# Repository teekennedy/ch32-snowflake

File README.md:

# CH32 Snowflake

A holiday snowflake with RGB LEDs, driven by the infamous CH32V003 microcontroller.

This is my first ever PCB design, and I borrowed heavily from [ch32-fireplace](https://github.com/johanwheeler/ch32-fireplace/tree/main) for snippets of schematic and code.

## PCB Shape

The snowflake shape was designed in OpenSCAD using the [BOSL2 library](https://github.com/BelfrySCAD/BOSL2).
If you want to view or make changes to the shape, I highly recommend installing the nightly version of openSCAD.

## KiCad Project

The KiCad project was designed with help from the [jlcpcb-tools plugin](https://github.com/Bouni/kicad-jlcpcb-tools).
If you plan to send this board to JLCPCB, be sure to import [corrections.csv](./board/jlcpcb/corrections.csv) before generating your pick and place file.
It has corrections for both the CH32V003 (90 degrees CCW rotation) and the TPS61002 boost converter (which is offset from where it should be).

I did my best to choose Basic parts where possible, to help keep the cost of the economic PCB assembly down.
Then I went with an ENIG coating and couldn't use economic PCBA anyway. Oh well.

## Firmware

In order to flash the firmware, you need to setup your build environment for [ch32fun](https://github.com/cnlohr/ch32fun).
See [their installation wiki](https://github.com/cnlohr/ch32fun/wiki/Installation) for instructions.

Next, build the `minichlink` utility.
Ensure the ch32fun submodule is initialized `git submodule update --init`.
Then, from the software/ch32fun/minichlink directory, run `make`.
If you have your RISC-V toolchain installed properly, it should build.

Now you can go to the software/src directory and run `make` to compile and flash the binary.

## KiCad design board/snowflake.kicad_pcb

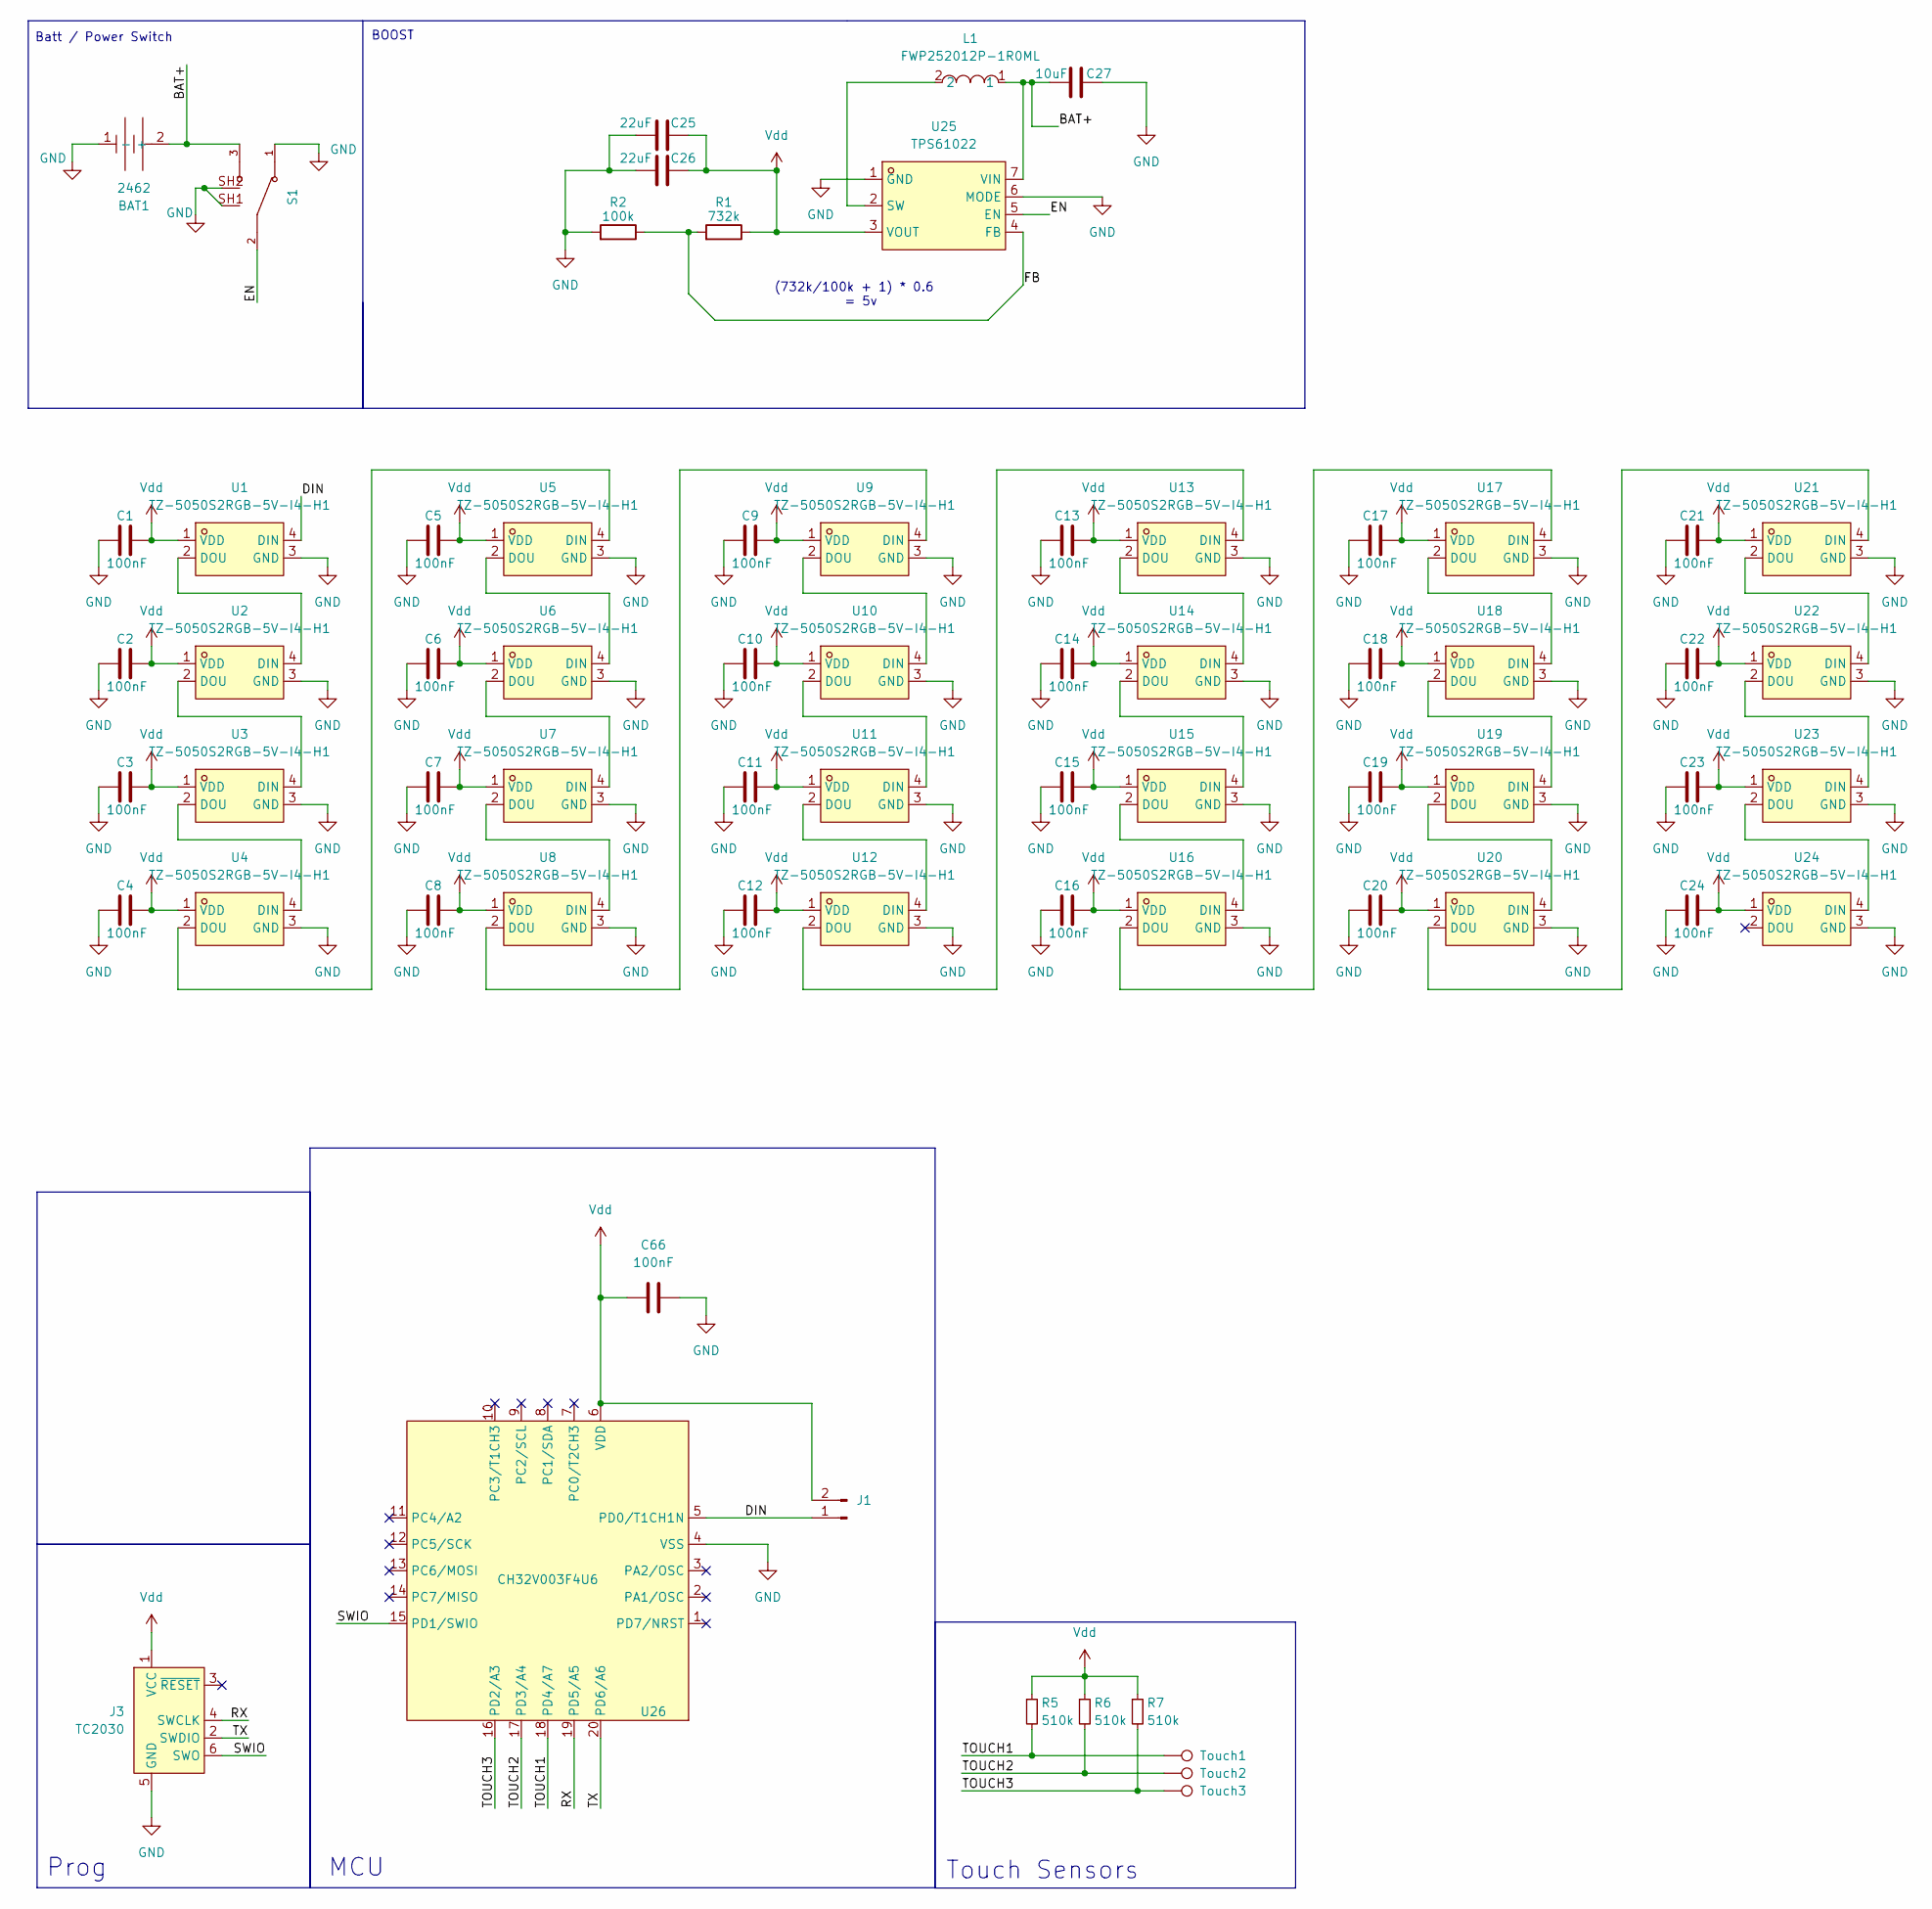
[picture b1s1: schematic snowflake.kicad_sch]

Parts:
BAT1: 2462; BAT-TH_2P-P14.50_2462; LCSC Part C3029547
C1, C2, C3, C4, C5, C6, C7, C8, C9, C10, C11, C12, C13, C14, C15, C16, C17, C18, C19, C20, C21, C22, C23, C24, C66: 100nF; C_0603_1608Metric; LCSC C14663
C25, C26: 22uF; C_0603_1608Metric; LCSC C59461
C27: 10uF; C_0603_1608Metric; LCSC C19702
J1: Conn_01x02_Pin; PinHeader_1x02_P2.54mm_Vertical
J3: TC2030; Tag-Connect_TC2030-IDC-NL_2x03_P1.27mm_Vertical
L1: FWP252012P-1R0ML; IND-SMD_L2.5-W2.0_YXMBL252010P; LCSC C5179444
R1: 732k; R_0603_1608Metric; LCSC C22961
R2: 100k; R_0402_1005Metric; LCSC C25741
R5, R6, R7: 510k; R_0603_1608Metric; MPN C23203; LCSC C23192
S1: SLW-1277545-3A-RA-N-D; SW_SLW-1277545-3A-RA-N-D; PARTREV 1.01
TP5: Touch1; TouchPad
TP6: Touch2; TouchPad
TP7: Touch3; TouchPad
U1, U2, U3, U4, U5, U6, U7, U8, U9, U10, U11, U12, U13, U14, U15, U16, U17, U18, U19, U20, U21, U22, U23, U24: TZ-5050S2RGB-5V-I4-H1; LED-SMD_4P-L5.0-W5.0-TL_WS2812B-B; LCSC C26167850
U25: TPS61022; VQFN-7_L2.0-W2.0-P0.55-TL_RWU; LCSC C915088
U26: CH32V003F4U6; QFN-20_L3.0-W3.0-P0.40-TL-EP1.7; MPN C5299908; LCSC C5299908

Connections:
/BAT+: BAT1.2 (+), C27.2, L1.1, S1.3, U25.7 (VIN)
/DIN: J1.1, U1.4 (DIN), U26.5 (PD0/T1CH1N)
/EN: S1.2, U25.5 (EN)
/FB: R1.2, R2.1, U25.4 (FB)
/RX: J3.4 (SWCLK), U26.19 (PD5/A5)
/SWIO: J3.6 (SWO), U26.15 (PD1/SWIO)
/TOUCH1: R5.2, TP5.1, U26.18 (PD4/A7)
/TOUCH2: R6.2, TP6.1, U26.17 (PD3/A4)
/TOUCH3: R7.2, TP7.1, U26.16 (PD2/A3)
/TX: J3.2 (SWDIO), U26.20 (PD6/A6)
GND: BAT1.1 (-), C1.1, C2.1, C3.1, C4.1, C5.1, C6.1, C7.1, C8.1, C9.1, C10.1, C11.1, C12.1, C13.1, C14.1, C15.1, C16.1, C17.1, C18.1, C19.1, C20.1, C21.1, C22.1, C23.1, C24.1, C25.2, C26.2, C27.1, C66.2, J3.5 (GND), R2.2, S1.1, S1.SH1, S1.SH2, U1.3 (GND), U2.3 (GND), U3.3 (GND), U4.3 (GND), U5.3 (GND), U6.3 (GND), U7.3 (GND), U8.3 (GND), U9.3 (GND), U10.3 (GND), U11.3 (GND), U12.3 (GND), U13.3 (GND), U14.3 (GND), U15.3 (GND), U16.3 (GND), U17.3 (GND), U18.3 (GND), U19.3 (GND), U20.3 (GND), U21.3 (GND), U22.3 (GND), U23.3 (GND), U24.3 (GND), U25.1 (GND), U25.6 (MODE), U26.4 (VSS), U26.21 (VSS)
unnamed: U1.2 (DOU), U2.4 (DIN)
unnamed: U2.2 (DOU), U3.4 (DIN)
unnamed: U3.2 (DOU), U4.4 (DIN)
unnamed: U4.2 (DOU), U5.4 (DIN)
unnamed: U5.2 (DOU), U6.4 (DIN)
unnamed: U6.2 (DOU), U7.4 (DIN)
unnamed: U7.2 (DOU), U8.4 (DIN)
unnamed: U8.2 (DOU), U9.4 (DIN)
unnamed: U9.2 (DOU), U10.4 (DIN)
unnamed: U10.2 (DOU), U11.4 (DIN)
unnamed: U11.2 (DOU), U12.4 (DIN)
unnamed: U12.2 (DOU), U13.4 (DIN)
unnamed: U13.2 (DOU), U14.4 (DIN)
unnamed: U14.2 (DOU), U15.4 (DIN)
unnamed: U15.2 (DOU), U16.4 (DIN)
unnamed: U16.2 (DOU), U17.4 (DIN)
unnamed: U17.2 (DOU), U18.4 (DIN)
unnamed: U18.2 (DOU), U19.4 (DIN)
unnamed: U19.2 (DOU), U20.4 (DIN)
unnamed: U20.2 (DOU), U21.4 (DIN)
unnamed: U21.2 (DOU), U22.4 (DIN)
unnamed: U22.2 (DOU), U23.4 (DIN)
unnamed: U23.2 (DOU), U24.4 (DIN)
unnamed: L1.2, U25.2 (SW)
Vdd: C1.2, C2.2, C3.2, C4.2, C5.2, C6.2, C7.2, C8.2, C9.2, C10.2, C11.2, C12.2, C13.2, C14.2, C15.2, C16.2, C17.2, C18.2, C19.2, C20.2, C21.2, C22.2, C23.2, C24.2, C25.1, C26.1, C66.1, J1.2, J3.1 (VCC), R1.1, R5.1, R6.1, R7.1, U1.1 (VDD), U2.1 (VDD), U3.1 (VDD), U4.1 (VDD), U5.1 (VDD), U6.1 (VDD), U7.1 (VDD), U8.1 (VDD), U9.1 (VDD), U10.1 (VDD), U11.1 (VDD), U12.1 (VDD), U13.1 (VDD), U14.1 (VDD), U15.1 (VDD), U16.1 (VDD), U17.1 (VDD), U18.1 (VDD), U19.1 (VDD), U20.1 (VDD), U21.1 (VDD), U22.1 (VDD), U23.1 (VDD), U24.1 (VDD), U25.3 (VOUT), U26.6 (VDD)

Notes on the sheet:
Batt / Power Switch
BOOST
Prog
Touch Sensors
(732k/100k + 1) * 0.6 = 5v
MCU

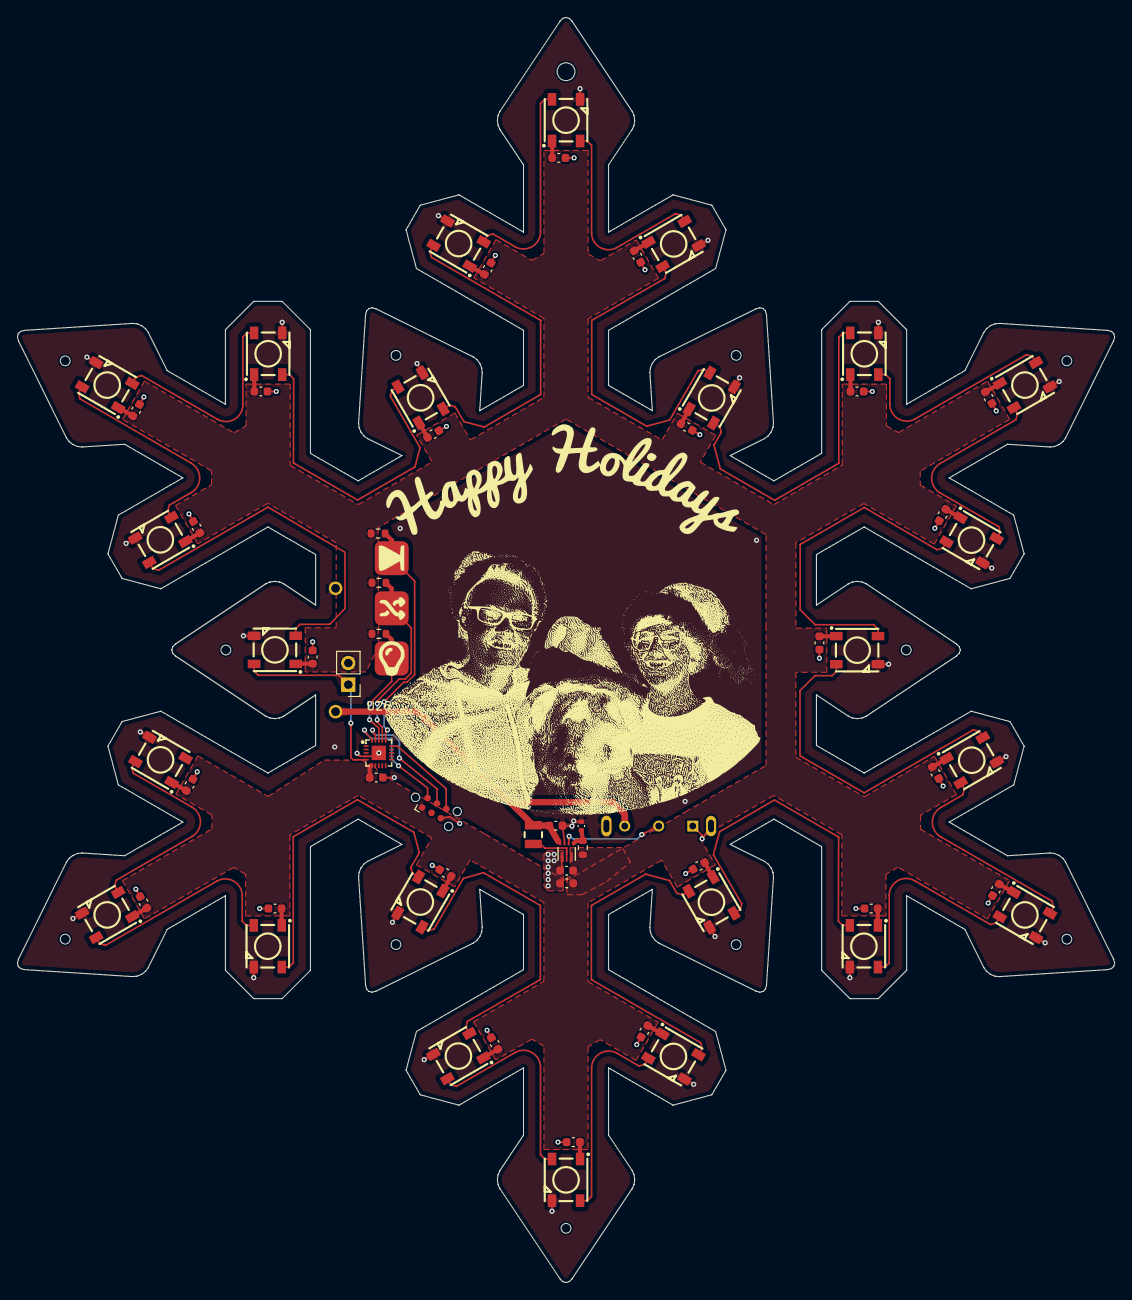
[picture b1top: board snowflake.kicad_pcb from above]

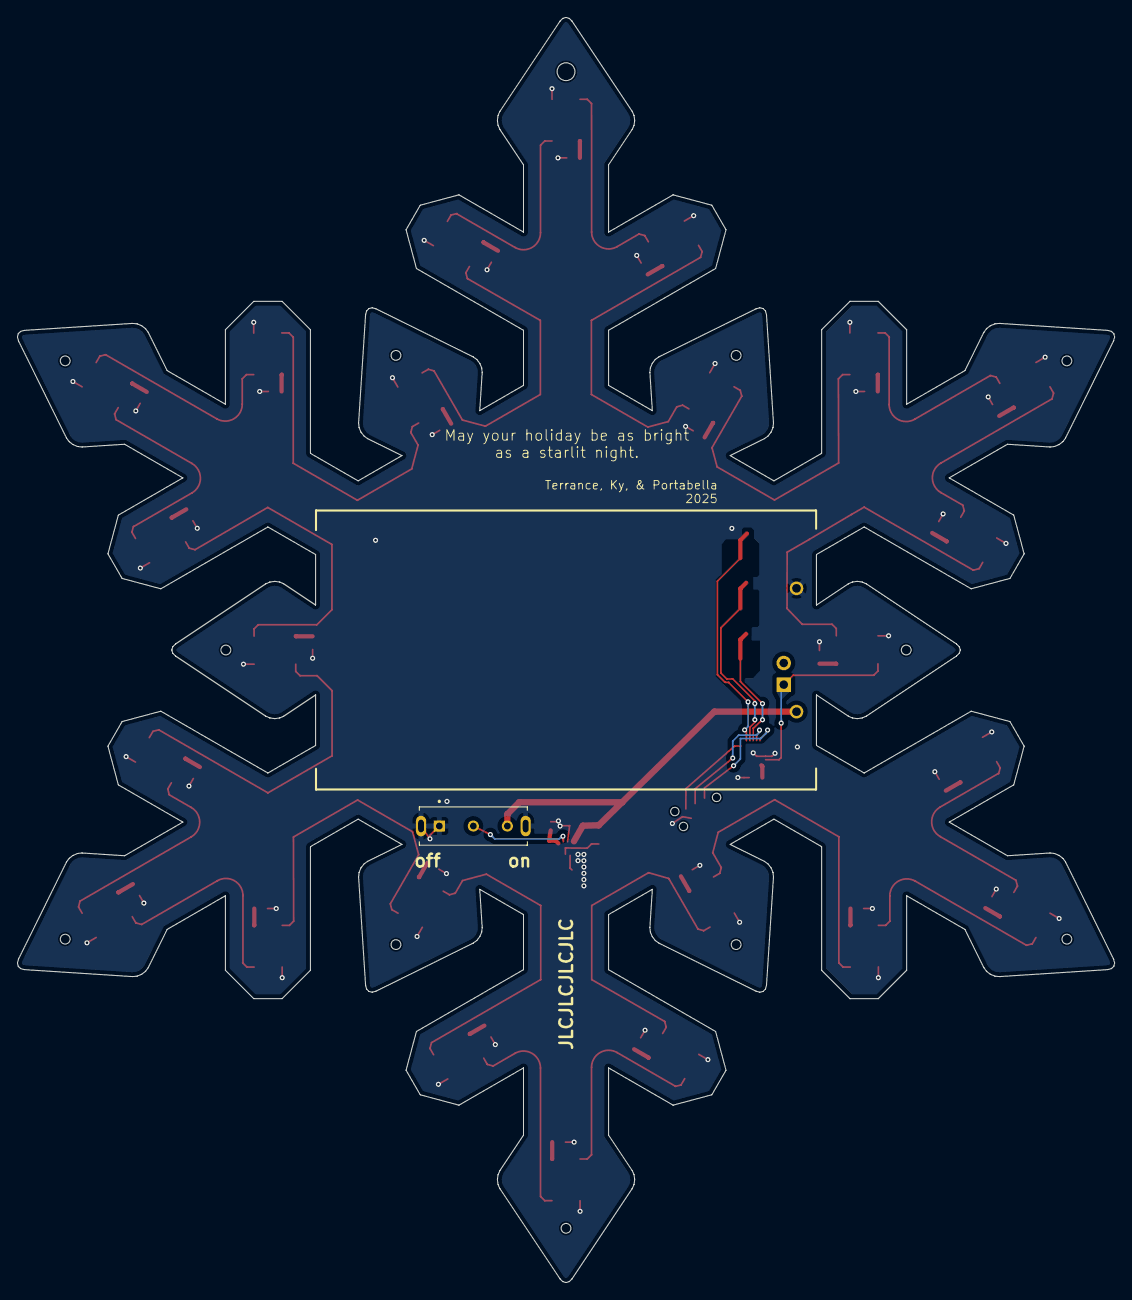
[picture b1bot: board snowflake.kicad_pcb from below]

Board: 2 copper layers, 129.0 x 148.8 mm, 67 parts (2 on the bottom side), 36 nets.

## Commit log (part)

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2025-11-08 snowflake shape with evenly spaced leds
2025-11-10 v1 snowflake shape
2025-11-10 Modularize hexagon shape
2025-11-10 About to create rotational array of LEDs
2025-11-11 2/6 branches
2025-11-11 Add JLCPCB Part Numbers
2025-11-11 Submitted for cost estimate from JLCPCB
2025-11-11 The nets are happy again
2025-11-13 Use zones instead of traces for +5V
2025-11-13 First prototype
2025-11-13 Add mounting and tooling holes
2025-11-13 Use basic parts, fix boost converter positioning
2025-11-13 Add more vias to try and keep the ground planes even
2025-11-14 Add teardrops to vias and PTH pads, mask border
2025-11-14 Remove lock file, update .gitignore
2025-11-24 put everything on one side
2025-11-26 initial import of software stack
2025-11-26 Get rainbow pattern working
2025-11-26 Update PCB and customize some footprints
2025-11-26 Add readme, update rgb led driver
2025-11-30 Get CH32V003 working
2025-11-30 Cleanup
2025-12-01 Add graphics to board
2025-12-01 Final board updates before sending
2025-12-01 Catch what would have been a huge mistake
2025-12-01 Cleanup power switch traces
2025-12-01 Submitted for production
2025-12-03 Add preview image
2025-12-03 Add missing 3d file for CH32v003 footprint
2025-12-12 Got as far as I could with DMA-based LED control
2025-12-20 Fix R1 part number
2025-12-20 Add JLCPCB pick and place corrections.csv
2025-12-20 Update variables based on button press
2025-12-20 Move touch code to subfolder, fix animations crashing
2025-12-21 Tweak brightness and twinkle animation
2025-12-21 Add nvram settings, multiple twinkle animations
2025-12-21 Add shooting star animation
2025-12-21 Make frame timing consistent across animations
2025-12-21 Implement shuffle functionality
2025-12-22 Add christmas lights animation
2026-01-02 Make touch button detection more robust
2026-01-02 Add small instruction card to go with snowflake
2026-01-12 Reduce brightness, add test animation
